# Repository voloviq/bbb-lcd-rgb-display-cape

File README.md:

# bbb-lcd-rgb-display-cape
Simple Beaglebone Black LCD display cape

PCB is designed for Orange Pi 2GIOT LCD Display

Board 3D View

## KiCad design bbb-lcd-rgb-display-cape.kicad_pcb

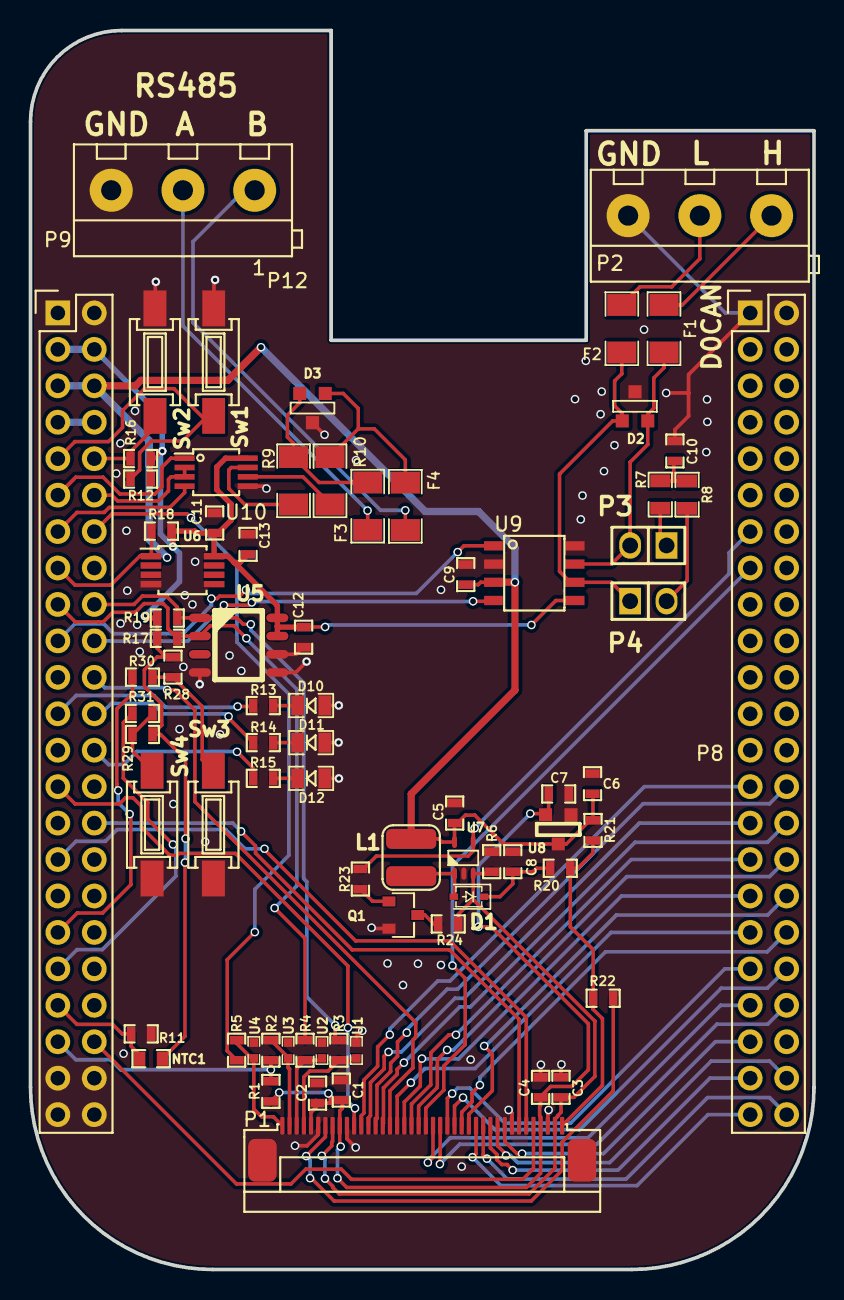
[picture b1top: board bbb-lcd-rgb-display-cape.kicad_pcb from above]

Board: 2 copper layers, 54.6 x 86.4 mm, 75 parts (0 on the bottom side), 78 nets.

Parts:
C1, C2, C3, C4: 100n/50V; 100nF_0603
C5: 1uF/6V3; 1uF_0603
C6, C7, C9, C10, C13: 100nF/50V; 100nF_0603
C8: 4.7uF/35V; 4_7uF_0603
C11, C12: 100n_50V; 100nF_0603
D1: NSR0530H-D; NSR0530H-D_SOD323
D2: PESD2CAN; PESD2CAN.215
D3: SM712.TCT
D10: LED_KP-2012HD; LED_KP-2012HD_SM0805
D11: LED_KP-2012SGD; LED_KP-2012SGD_SM0805
D12: LED_KP-2012YD; LED_KP-2012YD_SM0805
F1, F2, F3, F4: SN005-60
L1: 4u7H_CD32_SMD_Coil; 4u7H_SMD_CD32
NTC1: NTCS0603E3103FMT
P1: OrangePi-2G-IOT LCD Interface; 40pin_fpc_0_5mm
P2: CAN BUS; DG301-5.0-03P-12-00A(H)
P3, P4: TERM; Goldpin_2_2_54mm
P8, P9: BeagleBone_Black_Header; Socket_BeagleBone_Black
P12: RS485; DG301-5.0-03P-12-00A(H)
Q1: BC847B; BC847B_SOT23
R1, R23: 10k; 10k_0603
R2, R3, R4, R5: 1k; 1k_0603
R6, R24: 10R/1%/0.1Wat; 10R_0603
R7, R8: 60.4R; 60.4R_0805
R9, R10: CRCW120610R0FKEAHP
R11, R12, R16, R17, R18, R19, R28, R29: 4k7; 4k7_0603
R13, R14, R15, R30, R31: 100R; 100R_0603
R20, R21, R22: 0R; 0R_0603
Sw1, Sw2, Sw3, Sw4: DTSM-31N; DTSM-31N_SMD
U1, U2, U3, U4: 82357120100
U5: TCN75A; TCN75A_SOIC8
U6: DS18B20U; DS18B20U_MSOP-8_3x3mm_P0.65mm
U7: TPS61169DCKR
U8: AP2127K-2.8TRG1; AP2127K-2.8TRG1_SOT23
U9: IFX1050GVIOXUMA1
U10: ISL3172EIUZ

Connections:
2V8: C1.1, C2.1, C4.1, C7.1, P1.4, P1.32 (P2), P1.36 (P6), R1.1, U8.2 (Vout)
3V3: C11.1, C12.1, C13.1, NTC1.2, P9.3, P9.4, R12.1, R16.1, R17.1, R18.1, R19.1, R28.1, R29.1, U5.7 (A0), U5.8 (VDD), U6.8 (VDD), U9.5 (V33V), U10.8 (VCC)
5V: C5.1, C6.1, C9.1, L1.1, P9.5, P9.6, R21.2, U7.5 (VIN), U8.3 (Vin), U9.3 (VCC)
/AN0: NTC1.1, P9.39, R11.1
/B1: P1.9, P8.41
/B2: P1.10, P8.44
/B3: P1.11 (P1), P8.43
/B4: P1.12 (P2), P8.46
/B5: P1.13 (P3), P8.45
/BACKLIGHT_PWM: P8.13, R23.1, U7.4 (CTRL)
/CAN/CAN_H: F1.2, P2.1
/CAN/CAN_L: F2.2, P2.2
/DCAN0_RX: P9.19, U9.1 (TxD)
/DCAN0_TX: P9.20, U9.4 (RxD)
/DE: P1.26 (P6), P8.30
/G0: P1.14 (P4), P8.34
/G1: P1.15 (P5), P8.36
/G2: P1.16 (P6), P8.38
/G3: P1.17 (P7), P8.37
/G4: P1.18 (P8), P8.40
/G5: P1.19 (P9), P8.39
/GPIO0_2: P1.25 (P5), P9.22
/GPIO0_14: P9.26, R15.1
/GPIO0_15: P9.24, R14.1
/GPIO0_20: P9.41, R1.2, R2.1
/GPIO1_16: P9.15, R18.2, U6.1 (DQ)
/GPIO1_17: P9.23, R13.1
/GPIO1_18: P9.14, R5.1
/GPIO1_28: P9.12, U10.2 (~RE), U10.3 (DE)
/GPIO3_19: P1.30 (P10), P9.27
/HSYNC: P1.28 (P8), P8.29
/I2C1_SCL: P9.17, R4.1, R17.2, U5.2 (SCL)
/I2C1_SDA: P9.18, R3.1, R19.2, U5.1 (SDA)
/LCD Display/BACKLIGHT_HIGH: C8.1, D1.1 (K), R20.1
/LCD Display/BACKLIGHT_LOW: C3.1, P1.2, P1.33 (P3), R6.1, R24.1, U7.3 (FB)
/LCD Display/BACKLIGHT_VDD: P1.1, R20.2, R21.1, R22.1
/PCLK: P1.27 (P7), P8.28
/PWR_BUT: P9.9, R12.2, Sw1.1
/R1: P1.20 (P10), P8.15
/R2: P1.21 (P1), P8.32
/R3: P1.22 (P2), P8.31
/R4: P1.23 (P3), P8.33
/R5: P1.24 (P4), P8.35
/RS485/RS485_A: F4.2, P12.1
/RS485/RS485_B: F3.2, P12.2
/SPI1_CS1: P1.5, P9.42
/SPI1_MOSI: P1.7, P9.30
/SPI1_SCK: P1.6, P9.31
/SYS_RESETN: P9.10, R16.2, Sw2.1
/UART4_RX: P9.11, U10.1 (RO)
/UART4_TX: P9.13, U10.4 (DI)
/VSYNC: P1.29 (P9), P8.27
GND: C1.2, C2.2, C3.2, C4.2, C5.2, C6.2, C7.2, C8.2, C9.2, C10.2, C11.2, C12.2, C13.2, D2.3 (GND), D3.3 (GND), D10.1 (A), D11.1 (A), D12.1 (A), P1.3, P1.8, P1.31 (P1), P1.35 (P5), P2.3, P8.1, P8.2, P9.1, P9.2, P9.43, P9.44, P9.45, P9.46, P12.3, Q1.2 (E), R6.2, R11.2, Sw1.2, Sw2.2, Sw3.2, Sw4.2, U1.1 (A), U2.1 (A), U3.1 (A), U4.1 (A), U5.4 (VSS), U5.5 (A2), U5.6 (A1), U6.4 (VSS), U7.2 (GND), U8.1 (Adj(GND)), U9.2 (GND), U9.8 (INH), U10.5 (GND)
unnamed: C10.1, R7.2, R8.1
unnamed: D1.2 (A), L1.2, U7.1 (SW)
unnamed: D2.1 (I/O1), F2.1, P4.1, U9.6 (CANL)
unnamed: D2.2 (I/O2), F1.1, P3.2, U9.7 (CANH)
unnamed: D3.1 (I/O1), F4.1, R10.1
unnamed: D3.2 (I/O2), F3.1, R9.1
unnamed: D10.2 (K), R13.2
unnamed: D11.2 (K), R14.2
unnamed: D12.2 (K), R15.2
unnamed: P1.34 (P4), R22.2
unnamed: P1.37 (P7), R3.2, U1.2 (K)
unnamed: P1.38 (P8), R4.2, U2.2 (K)
unnamed: P1.39 (P9), R2.2, U3.2 (K)
unnamed: P1.40 (P10), R5.2, U4.2 (K)
unnamed: P3.1, R7.1
unnamed: P4.2, R8.2
unnamed: P9.35, R30.2
unnamed: P9.37, R31.2
unnamed: R9.2, U10.7 (B/Z)
unnamed: R10.2, U10.6 (A/Y)
unnamed: Q1.1 (B), R23.2
unnamed: Q1.3 (C), R24.2
unnamed: R28.2, R30.1, Sw3.1
unnamed: R29.2, R31.1, Sw4.1
SYS_5V: P9.7, P9.8

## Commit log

2021-04-14 Added LCD image
2021-04-14 Initial
2021-04-14 Continue schematic work
2021-04-14 Added original orangepi 2giot schematic
2021-04-14 Corrected schematic and added new elements
2021-04-27 Finalized project
2021-04-27 Updated display pwm backlight section, regenerated gerbers again
2021-04-29 Regenerated gerbers
